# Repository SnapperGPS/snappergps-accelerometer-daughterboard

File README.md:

# snappergps-accelerometer-daughterboard

*Author: Jonas Beuchert*

Accelerometer daughterboard for a basic SnapperGPS receiver.

## Table of contents

* [Files](#files)
* [Manufacturing](#manufacturing)
* [Components](#components)
* [Assembly](#assembly)
* [Flashing](#flashing)
* [Usage](#usage)
* [Acknowledgements](#acknowledgements)

## Files

* `accelerometer-daughterboard.brd`: PCB layout file for the daughterboard. Created with Autodesk Eagle.
* `accelerometer-daughterboard`: Schematic file for the daughterboard. Created with Autodesk Eagle.
* `CAMOutputs`: Gerber files and drill file for manufacturing the daughterboard.
* `accelerometer-daughterboard.mnt` and `accelerometer-daughterboard.mnb`: Centroid files (top and bottom) for assembly.

## Manufacturing

* Get some PCBs manufactured by a PCB manufacturer of your choice.
(I used [Aisler](https://aisler.net/) or [PCBWay](https://www.pcbway.com/) in the past.)
For this, upload the `.brd` file or the `CAMOutputs` folder to the manufacturer's website.
Choose a two-layered PCB with size 3.74 mm x 11.94 mm.

* If you want, you can also let the manufacturer assemble the board(s) for you.

## Components

* 2x 10 kOhm resistor (footprint 0603), e.g., [RK73H1JTTD1002F](https://octopart.com/rk73h1jttd1002f-koa+speer-2166376).
* 1x [LIS3DH](https://www.st.com/en/mems-and-sensors/lis3dh.html) 3-axis MEMS accelerometer.

## Assembly

* Solder the two resistors and the accelerometer on the daughterboard.
Ensure that the pin-1 dot on the accelerometer is aligned with the dot on the PCB.
I recommend solder paste and a hot plate (or hot air gun) for soldering.

* Solder the assembled daughterboard on a basic SnapperGPS receiver.
The five pads on the back of the daughterboard should connect to the five pads on the SnapperGPS receiver.
The pads labeled `VDD` shall align.

## Flashing

* Go to [https://snappergps.info/flash](https://snappergps.info/flash).
* Connect the SnapperGPS receiver to your computer via USB.
* Pair the SnapperGPS receiver.
* Select the `SnapperGPS-Accelerometer` firmware.
* Flash the firmware.

## Usage

Find instructions in [the firmware repository](https://github.com/SnapperGPS/snappergps-firmware/blob/main/firmware_versions/snapper-accelerometer/README.md).

|   | 
|:--:| 
| *Figures 1 & 2: SnapperGPS V2.0.0 with accelerometer daughterboard.* |

## Acknowledgements

This SnapperGPS daughter-board was developed by
[Jonas Beuchert](https://users.ox.ac.uk/~kell5462/)
in the Department of Computer Science
of the University of Oxford.

Jonas Beuchert is
funded by the EPSRC Centre for Doctoral Training in
Autonomous Intelligent Machines and Systems
(DFT00350-DF03.01) and develops
SnapperGPS as part of his doctoral studies.
The implementation of SnapperGPS 
was co-funded by an EPSRC IAA Technology Fund
(D4D00010-BL14).

Parts of the design are based on the [Adafruit LIS3DH Triple-Axis Accelerometer (+-2g/4g/8g/16g) PCB](https://github.com/adafruit/Adafruit-LIS3DH-Breakout-PCB), e.g., footprints.
It was designed by Limor Fried/Ladyada for Adafruit Industries.
Find the original readme [here](adafruit-readme.md).

This repository is licensed under a
[Creative Commons Attribution 3.0 International License][cc-by].

[![CC BY 3.0][cc-by-image]][cc-by]

[cc-by]: http://creativecommons.org/licenses/by/3.0/
[cc-by-image]: https://i.creativecommons.org/l/by/3.0/88x31.png

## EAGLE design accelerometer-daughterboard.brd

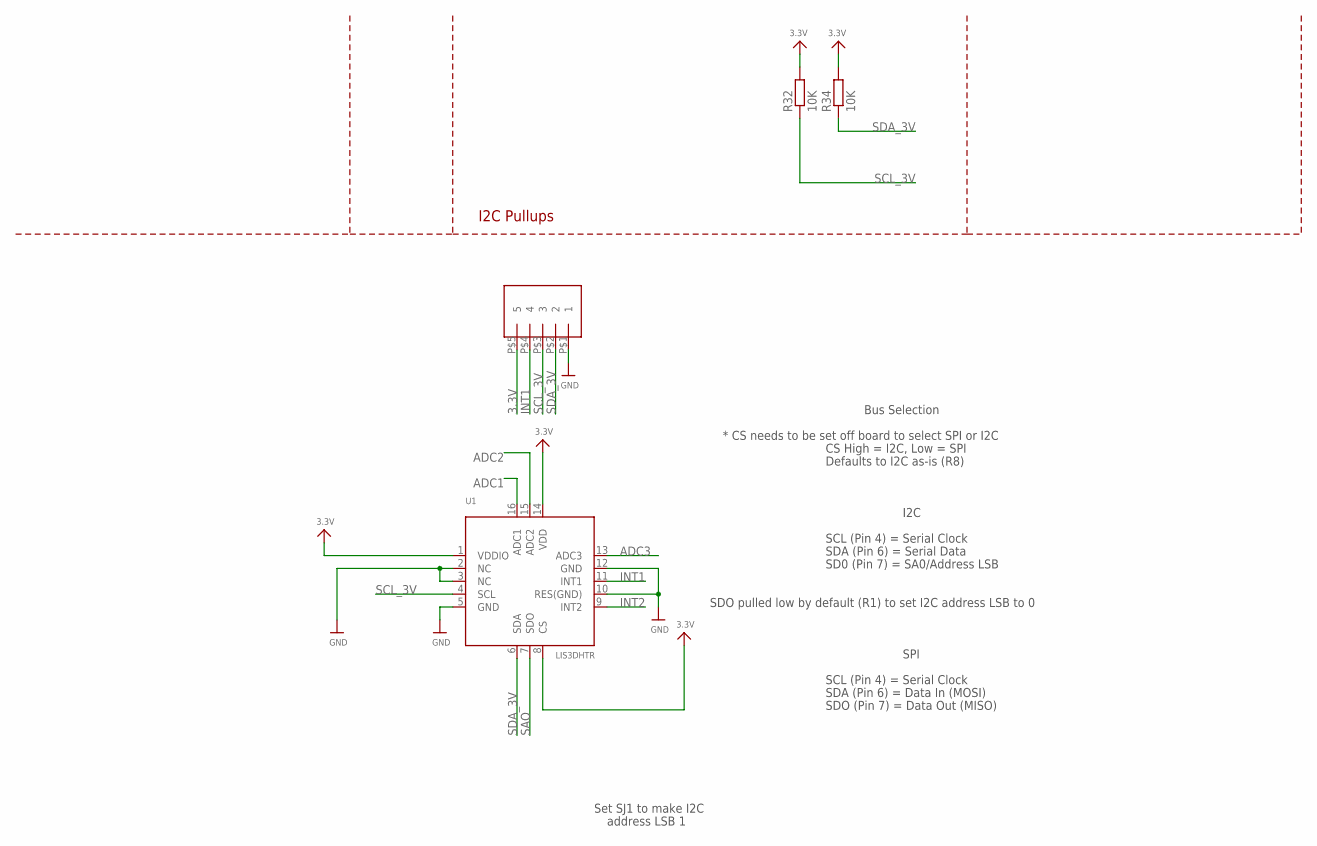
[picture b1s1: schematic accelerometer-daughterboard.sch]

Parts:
R32, R34: 10K; R0603
U1: LIS3DHTR; LGA16_3X3MM
U$1: ALEX_CONN5

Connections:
3.3V: R32.2, R34.2, U1.1 (VDDIO), U1.8 (CS), U1.14 (VDD), U$1.P$5 (5)
ADC1: U1.16 (ADC1)
ADC2: U1.15 (ADC2)
ADC3: U1.13 (ADC3)
GND: U1.2 (NC), U1.3 (NC), U1.5 (GND), U1.10 (RES(GND)), U1.12 (GND), U$1.P$1 (1)
INT1: U1.11 (INT1), U$1.P$4 (4)
INT2: U1.9 (INT2)
SAO: U1.7 (SDO)
SCL_3V: R32.1, U1.4 (SCL), U$1.P$3 (3)
SDA_3V: R34.1, U1.6 (SDA), U$1.P$2 (2)

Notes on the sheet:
I2C Pullups
I2C
SCL (Pin 4) = Serial Clock
SDA (Pin 6) = Serial Data
SD0 (Pin 7) = SA0/Address LSB
* CS needs to be set off board to select SPI or I2C
CS High = I2C, Low = SPI
Defaults to I2C as-is (R8)
SDO pulled low by default (R1) to set I2C address LSB to 0
Bus Selection
SPI
SDA (Pin 6) = Data In (MOSI)
SDO (Pin 7) = Data Out (MISO)
Set SJ1 to make I2C
address LSB 1

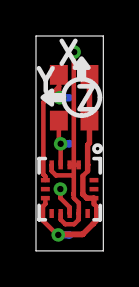
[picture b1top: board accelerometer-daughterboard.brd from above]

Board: 2 copper layers, 3.7 x 11.9 mm, 4 parts (1 on the bottom side), 5 nets.

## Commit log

2023-06-26 Add initial files
2023-06-26 Remove power supply (have 3.3 V already)
2023-06-26 Remove LED
2023-06-26 Remove I2C level-shifting
2023-06-26 Remove connector headers
2023-06-26 Remove through-holes
2023-06-26 Hardwire CS to I2C mode; add pads; remove un-used board elements
2023-06-26 USe 0603 resistors
2023-06-26 Add vias; remove some wires
2023-06-26 Complete first board draft, including outline and wiring
2023-06-26 Rename SD0 to SA0; add measures
2023-06-26 Change measures layer
2023-06-26 Add .gitignore
2023-06-28 Tweak
2023-06-28 Re-add buffer caps
2023-06-28 remove caps again
2023-06-28 Remove logo
2023-06-28 Change attribute
2023-07-18 Add gerber files and drill files
2023-07-18 Add READMEs, license, images
2023-07-18 Add .zip to .gitignore
2023-07-18 Change filenames in README
2023-07-21 Update flashing isntructions after web app update
2023-12-02 Add centroid files for assembly

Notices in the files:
parts and their libraries:
microbuilder: This work is placed in the public domain, and may be freely used for commercial and non-commercial work with the following conditions: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
